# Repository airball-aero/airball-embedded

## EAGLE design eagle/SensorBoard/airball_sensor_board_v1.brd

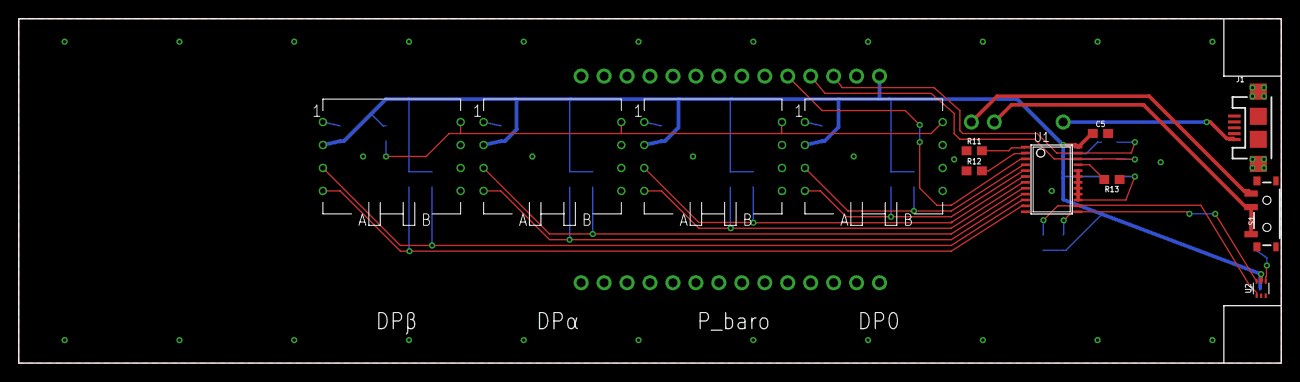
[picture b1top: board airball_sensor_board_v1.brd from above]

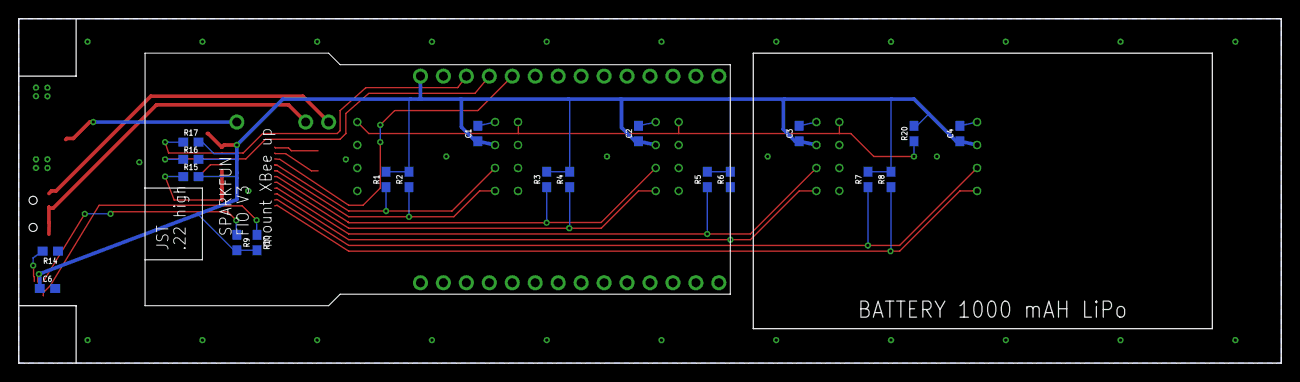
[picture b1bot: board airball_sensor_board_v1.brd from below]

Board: 2 copper layers, 139.7 x 38.1 mm, 33 parts (21 on the bottom side), 24 nets.

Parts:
C1, C2, C3, C4, C5, C6: 4.7uF; 0603
J1: USB-MICROB
R1, R2, R3, R4, R5, R6, R7, R8, R9, R10, R11, R12, R13, R14, R15, R16, R17, R20: 4.7k; 0603
S1: SWITCH_SPST_SMD_A
U1: TSSOP24
U2: TMP102; SOT563
U$2: SPARKFUN_FIO_V3
UP1, UP2, UP3, UP4: ALL_SENSORS_E1BD_8PIN_THRU

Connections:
#I2C_RST: U1.3, U$2.P$5
GND: C1.2, C2.2, C3.2, C4.2, C5.2, C6.2, J1.GND, R11.1, R12.1, R13.1, R14.1, U1.12, U2.2, U$2.P$2, U$2.P$28, UP1.P$1, UP2.P$1, UP3.P$1, UP4.P$1
unnamed: R1.1, U1.4, UP1.P$3
unnamed: R2.1, U1.5, UP1.P$4
unnamed: R3.1, U1.6, UP2.P$3
unnamed: R4.1, U1.7, UP2.P$4
unnamed: R5.1, U1.8, UP3.P$3
unnamed: R6.1, U1.9, UP3.P$4
unnamed: R7.1, U1.10, UP4.P$3
unnamed: R8.1, U1.11, UP4.P$4
unnamed: S1.1, U$2.P$29
unnamed: J1.VBUS, U$2.P$31
unnamed: R13.2, U1.21
unnamed: R12.2, U1.2
unnamed: R11.2, U1.1
unnamed: R20.1, UP1.P$8, UP2.P$8, UP3.P$8, UP4.P$8
unnamed: R9.1, U1.13, U2.6
unnamed: R10.1, U1.14, U2.1
unnamed: S1.2, S1.3, U$2.P$30
unnamed: R14.2, U2.4
unnamed: R15.1, U1.15, U1.16, U1.17, U1.18, U1.19, U1.20
SCL_IN: R16.1, U1.22, U$2.P$4
SDA_IN: R17.1, U1.23, U$2.P$3
VCC: C1.1, C2.1, C3.1, C4.1, C5.1, C6.1, R1.2, R2.2, R3.2, R4.2, R5.2, R6.2, R7.2, R8.2, R9.2, R10.2, R15.2, R16.2, R17.2, R20.2, U1.24, U2.5, U$2.P$1, U$2.P$26, UP1.P$2, UP2.P$2, UP3.P$2, UP4.P$2

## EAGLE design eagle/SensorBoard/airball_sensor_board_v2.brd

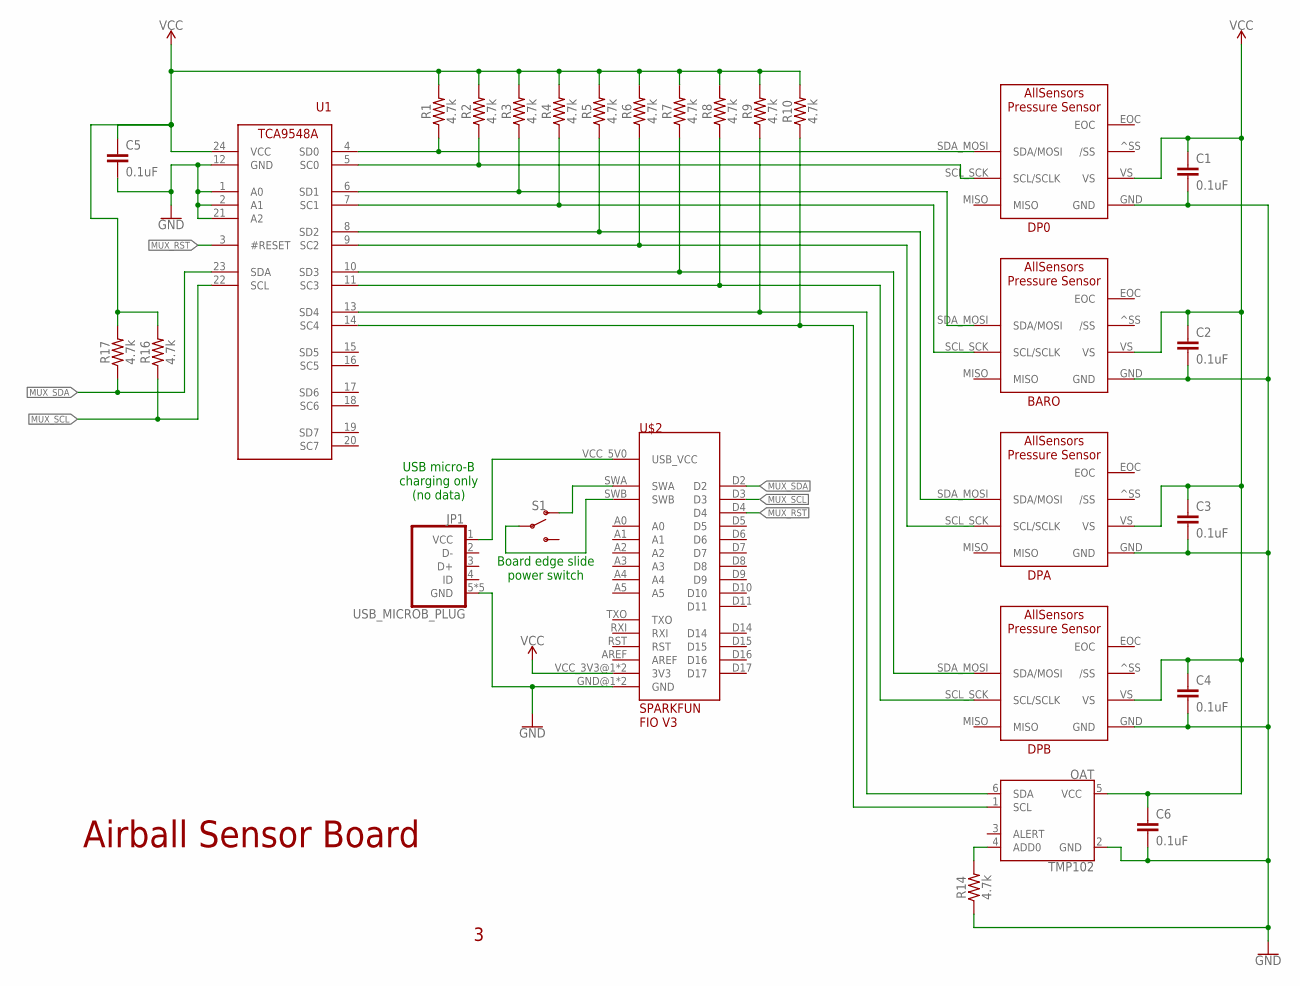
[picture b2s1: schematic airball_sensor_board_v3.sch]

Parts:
BARO: ALL_SENSORS_DLHR_E1ND; ALL_SENSORS_E1BD_8PIN_THRU
C1, C2, C3, C4, C5, C6: 0.1uF; 0603
DP0: ALL_SENSORS_DLHR_E1ND; ALL_SENSORS_E1BD_8PIN_THRU
DPA: ALL_SENSORS_DLHR_E1ND; ALL_SENSORS_E1BD_8PIN_THRU
DPB: ALL_SENSORS_DLHR_E1ND; ALL_SENSORS_E1BD_8PIN_THRU
JP1: USB_MICROB_PLUG; USB_MICRO_B_TYCO
OAT: TMP102; SOT563
R1, R2, R3, R4, R5, R6, R7, R8, R9, R10, R14, R16, R17: 4.7k; 0603
S1: SWITCH-SPDT-SMD-RIGHT-ANGLE; SWITCH_SPST_SMD_A
U1: TCA9548ATSSOP24; TSSOP24
U$2: SPARKFUN_FIO_V3

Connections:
GND: BARO.GND, C1.2, C2.2, C3.2, C4.2, C5.2, C6.2, DP0.GND, DPA.GND, DPB.GND, JP1.5 (GND), JP1.SH@1 (GND), JP1.SH@2 (GND), JP1.SH@3 (GND), JP1.SH@4 (GND), OAT.2 (GND), R14.1, U1.1 (A0), U1.2 (A1), U1.12 (GND), U1.21 (A2), U$2.GND@1 (GND), U$2.GND@2 (GND)
MUX_RST: U1.3 (#RESET), U$2.D4
MUX_SCL: R16.1, U1.22 (SCL), U$2.D3
MUX_SDA: R17.1, U1.23 (SDA), U$2.D2
OAT_ADD0: OAT.4 (ADD0), R14.2
SCL_BARO: BARO.SCL_SCK (SCL/SCLK), R4.1, U1.7 (SC1)
SCL_DP0: DP0.SCL_SCK (SCL/SCLK), R2.1, U1.5 (SC0)
SCL_DPA: DPA.SCL_SCK (SCL/SCLK), R6.1, U1.9 (SC2)
SCL_DPB: DPB.SCL_SCK (SCL/SCLK), R8.1, U1.11 (SC3)
SCL_OAT: OAT.1 (SCL), R10.1, U1.14 (SC4)
SDA_BARO: BARO.SDA_MOSI (SDA/MOSI), R3.1, U1.6 (SD1)
SDA_DP0: DP0.SDA_MOSI (SDA/MOSI), R1.1, U1.4 (SD0)
SDA_DPA: DPA.SDA_MOSI (SDA/MOSI), R5.1, U1.8 (SD2)
SDA_DPB: DPB.SDA_MOSI (SDA/MOSI), R7.1, U1.10 (SD3)
SDA_OAT: OAT.6 (SDA), R9.1, U1.13 (SD4)
SWA: S1.1 (O), U$2.SWA
SWB: S1.2, U$2.SWB
VCC_3V3: BARO.VS, C1.1, C2.1, C3.1, C4.1, C5.1, C6.1, DP0.VS, DPA.VS, DPB.VS, OAT.5 (VCC), R1.2, R2.2, R3.2, R4.2, R5.2, R6.2, R7.2, R8.2, R9.2, R10.2, R16.2, R17.2, U1.24 (VCC), U$2.VCC_3V3@1 (3V3), U$2.VCC_3V3@2 (3V3)
VCC_USB: JP1.1 (VCC), U$2.VCC_5V0 (USB_VCC)

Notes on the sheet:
USB micro-B charging only (no data)
Board edge slide power switch
Airball Sensor Board

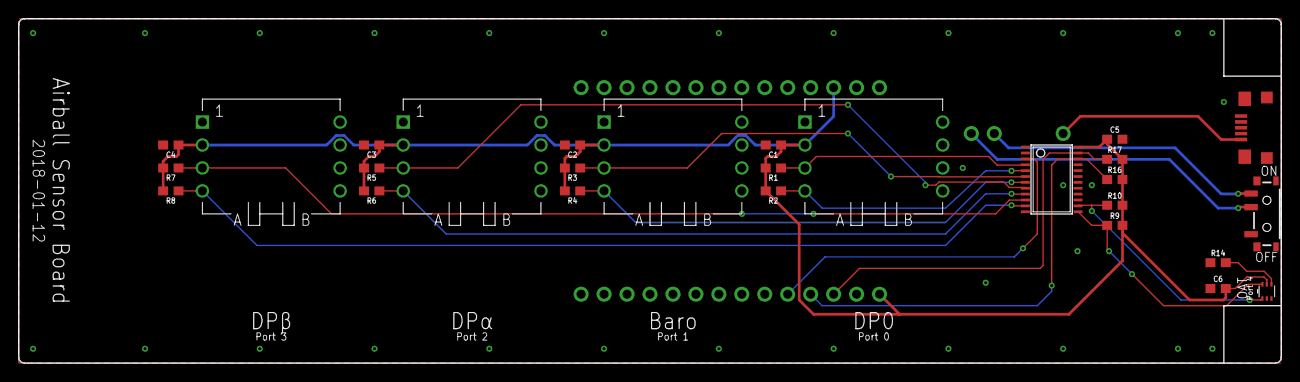
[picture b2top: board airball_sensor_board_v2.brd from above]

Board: 2 copper layers, 139.7 x 38.1 mm, 28 parts (1 on the bottom side), 19 nets.

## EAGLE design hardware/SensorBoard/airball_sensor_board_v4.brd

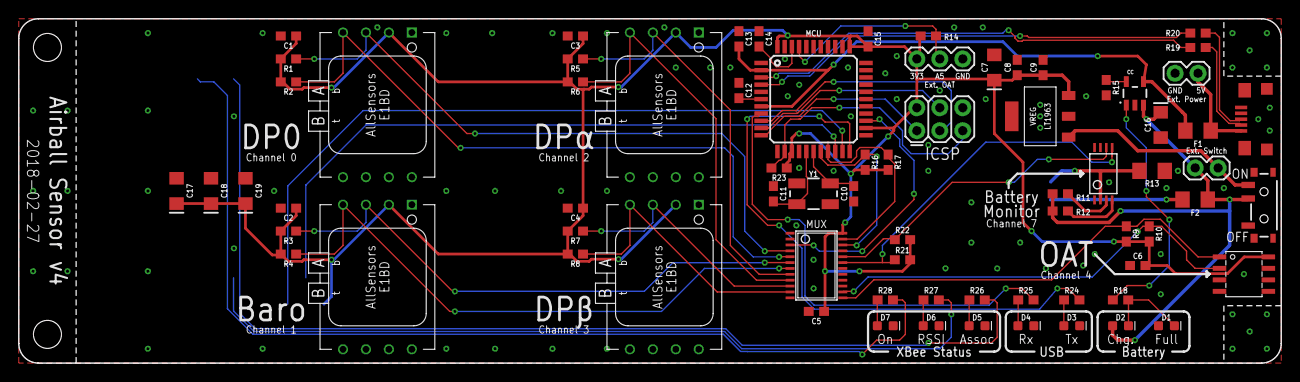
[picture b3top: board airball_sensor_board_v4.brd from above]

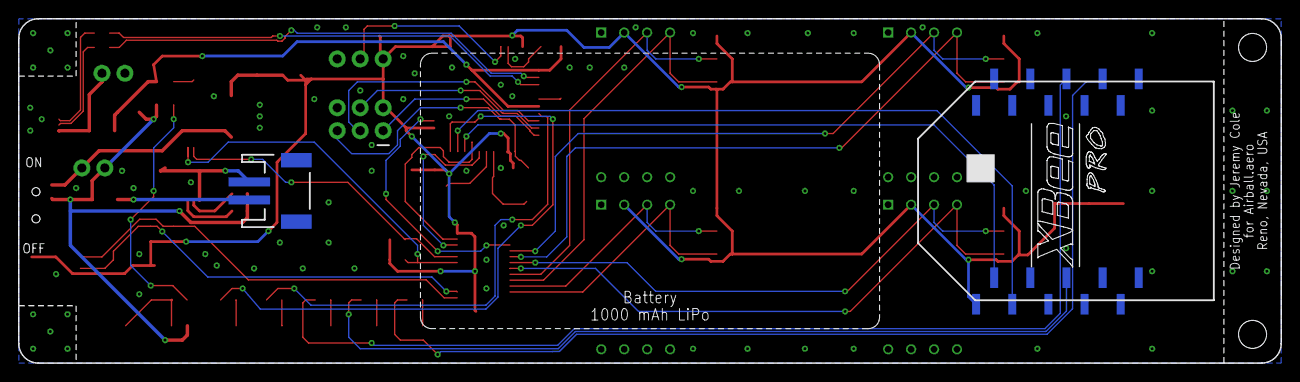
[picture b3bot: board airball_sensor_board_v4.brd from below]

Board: 2 copper layers, 139.7 x 38.1 mm, 76 parts (3 on the bottom side), 53 nets.

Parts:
BARO: ALLSENSORS_E1BD
BM: DS2782; TSSOP8
C1, C2, C3, C4, C5, C6, C9, C14, C15: 0.1uF; 0603
C7, C16, C17, C18, C19: 10uF; EIA3216
C8, C12, C13: 1.0uF; 0603
C10, C11: 22pF; 0603
CC: MCP73831; SOT23-5
D1, D2, D3, D4, D5, D6, D7: LED-0603
DP0: ALLSENSORS_E1BD
DPA: ALLSENSORS_E1BD
DPB: ALLSENSORS_E1BD
EXT_OAT: 1X03
EXT_POWER: 1X02
EXT_SW: 1X02
F1, F2: 6V/0.5A; 1206
ICSP: AVR_SPI_PROG_3X2PTH; 2X3
J1: JST-2-SMD
JP1: USB_MICROB_PLUG; USB_MICRO_B_TYCO
MCU: 32U4; TQFP44
MUX: TSSOP24
OAT: TMP275; SOIC8
R1, R2, R3, R4, R5, R6, R7, R8, R9, R10, R14, R16, R17, R21, R22: 4.7k; 0603
R11: 1k; 0603
R12: 470; 0603
R13: 15m; 1206
R15: 2.0k; 0603
R18, R24, R25, R26, R27, R28: 330; 0603
R19, R20: 22; 0603
R23: 10k; 0603
S1: SWITCH_SPST_SMD_A
U$3: LIPO_BATTERY_OUTLINE-1000MAH; SPARKFUN_LIPO_1000MAH
VREG: LT1963; SOT223-3
XBEE: XBEE-PRO-SMD
Y1: 8MHz; CRYSTAL-SMD-5X3.2-4PAD

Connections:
ASSOC_LED: R26.2, XBEE.15
BAT+: C16.+, CC.3, D2.A, EXT_SW.1, F2.2, R11.2, R12.2, S1.2
BAT+_UF: F2.1, J1.2
BAT-: BM.2, J1.1, R13.1
BAT_VRAW: EXT_SW.2, S1.1, VREG.1
BM_VDD: BM.4, R12.1
BM_VIN: BM.3, R11.1
CC_PROG: CC.5, R15.2
CHG_LED: CC.1, R18.1
EXT_OAT: EXT_OAT.2, MCU.41, R14.1
GND: BARO.1, BM.7, C1.2, C2.2, C3.2, C4.2, C5.2, C6.2, C7.-, C8.2, C9.2, C10.1, C11.1, C12.1, C13.1, C14.1, C15.1, C16.-, C17.-, C18.-, C19.-, CC.2, D1.A, D3.C, D4.C, D5.C, D6.C, D7.C, DP0.1, DPA.1, DPB.1, EXT_OAT.3, EXT_POWER.2, ICSP.6, JP1.5, JP1.SH@1, JP1.SH@2, JP1.SH@3, JP1.SH@4, MCU.5, MCU.15, MCU.23, MCU.33, MCU.35, MCU.43, MUX.1, MUX.2, MUX.12, MUX.21, OAT.4, OAT.5, OAT.6, OAT.7, R13.2, R15.1, VREG.2, VREG.TAB, XBEE.10
MISO: ICSP.1, MCU.11
MOSI: ICSP.4, MCU.10
MUX_RST: MCU.25, MUX.3
MUX_SCL: MCU.18, MUX.22, R16.1
MUX_SDA: MCU.19, MUX.23, R17.1
unnamed: D1.C, D2.C, R18.2
unnamed: C10.2, MCU.17, Y1.3
unnamed: C11.2, MCU.16, Y1.1
unnamed: D3.A, R24.1
unnamed: C14.2, MCU.42
unnamed: D4.A, R25.1
unnamed: C12.2, MCU.6
unnamed: D5.A, R26.1
unnamed: D6.A, R27.1
unnamed: D7.A, R28.1
ON_LED: R28.2, XBEE.13
RSSI_LED: R27.2, XBEE.6
RST: ICSP.5, MCU.13, R23.2
RXD: MCU.20, XBEE.2
RX_LED: MCU.8, R25.2
SCK: ICSP.3, MCU.9
SCL_BARO: BARO.4, MUX.7, R4.1
SCL_BM: BM.6, MUX.20, R22.1
SCL_DP0: DP0.4, MUX.5, R2.1
SCL_DPA: DPA.4, MUX.9, R6.1
SCL_DPB: DPB.4, MUX.11, R8.1
SCL_OAT: MUX.14, OAT.2, R10.1
SDA_BARO: BARO.3, MUX.6, R3.1
SDA_BM: BM.5, MUX.19, R21.1
SDA_DP0: DP0.3, MUX.4, R1.1
SDA_DPA: DPA.3, MUX.8, R5.1
SDA_DPB: DPB.3, MUX.10, R7.1
SDA_OAT: MUX.13, OAT.1, R9.1
TXD: MCU.21, XBEE.3
TX_LED: MCU.22, R24.2
USB_5V0_UF: EXT_POWER.1, F1.1, JP1.1
USB_N: MCU.3, R19.2
USB_P: MCU.4, R20.2
USB_X_N: JP1.2, R19.1
USB_X_P: JP1.3, R20.1
VCC_3V3: BARO.2, C1.1, C2.1, C3.1, C4.1, C5.1, C6.1, C7.+, C8.1, C9.1, C15.2, C17.+, C18.+, C19.+, DP0.2, DPA.2, DPB.2, EXT_OAT.1, ICSP.2, MCU.14, MCU.24, MCU.34, MCU.44, MUX.24, OAT.8, R1.2, R2.2, R3.2, R4.2, R5.2, R6.2, R7.2, R8.2, R9.2, R10.2, R14.2, R16.2, R17.2, R21.2, R22.2, R23.1, VREG.3, XBEE.1
VCC_5V0: C13.2, CC.4, F1.2, MCU.2, MCU.7

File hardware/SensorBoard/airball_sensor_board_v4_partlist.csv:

Partlist

Exported from airball_sensor_board_v4.brd at 2/25/20 10:12 PM

EAGLE Version 9.5.2 Copyright (c) 1988-2019 Autodesk, Inc.

Assembly variant: 

Part      Value               Package                Library             Position (mil)        Orientation

BARO                          ALLSENSORS_E1BD        airball             (1562.5 375)          R270
BM        DS2782              TSSOP8                 airball             (4725 825)            R0
C1        0.1uF               0603                   SparkFun-Capacitors (1175 1425)           R180
C2        0.1uF               0603                   SparkFun-Capacitors (1175 675)            R180
C3        0.1uF               0603                   SparkFun-Capacitors (2425 1425)           R180
C4        0.1uF               0603                   SparkFun-Capacitors (2425 675)            R180
C5        0.1uF               0603                   SparkFun-Capacitors (3475 225)            R180
C6        0.1uF               0603                   SparkFun-Capacitors (4875 425)            R180
C7        10uF                EIA3216                SparkFun-Capacitors (4250 1287.5)         R270
C8        1.0uF               0603                   SparkFun-Capacitors (4350 1287.5)         R90
C9        0.1uF               0603                   SparkFun-Capacitors (4462.5 1287.5)       R90
C10       22pF                0603                   SparkFun-Capacitors (3637.5 737.5)        R90
C11       22pF                0603                   SparkFun-Capacitors (3287.5 737.5)        R270
C12       1.0uF               0603                   SparkFun-Capacitors (3137.5 1187.5)       R270
C13       1.0uF               0603                   SparkFun-Capacitors (3137.5 1412.5)       R270
C14       0.1uF               0603                   SparkFun-Capacitors (3225 1412.5)         R270
C15       0.1uF               0603                   SparkFun-Capacitors (3700 1412.5)         R270
C16       10uF                EIA3216                SparkFun-Capacitors (4975 1037.5)         R90
C17       10uF                EIA3216                SparkFun-Capacitors (687.5 750)           R270
C18       10uF                EIA3216                SparkFun-Capacitors (837.5 750)           R270
C19       10uF                EIA3216                SparkFun-Capacitors (987.5 750)           R270
CC        MCP73831            SOT23-5                SparkFun-IC-Power   (4862.5 1175)         R0
D1                            LED-0603               SparkFun-LED        (5000 162.5)          R0
D2                            LED-0603               SparkFun-LED        (4800 162.5)          R0
D3                            LED-0603               SparkFun-LED        (4587.5 162.5)        R0
D4                            LED-0603               SparkFun-LED        (4387.5 162.5)        R0
D5                            LED-0603               SparkFun-LED        (4175 162.5)          R0
D6                            LED-0603               SparkFun-LED        (3975 162.5)          R0
D7                            LED-0603               SparkFun-LED        (3775 162.5)          R0
DP0                           ALLSENSORS_E1BD        airball             (1562.5 1125)         R270
DPA                           ALLSENSORS_E1BD        airball             (2812.5 1125)         R270
DPB                           ALLSENSORS_E1BD        airball             (2812.5 375)          R270
EXT_OAT                       1X03                   SparkFun-Connectors (3912.5 1325)         R0
EXT_POWER                     1X02                   SparkFun-Connectors (5137.5 1262.5)       R180
EXT_SW                        1X02                   SparkFun-Connectors (5125 850)            R0
F1        6V/0.5A             1206                   SparkFun-Fuses      (5137.5 1012.5)       R180
F2        6V/0.5A             1206                   SparkFun-Fuses      (5125 712.5)          R0
ICSP      AVR_SPI_PROG_3X2PTH 2X3                    SparkFun-Connectors (3912.5 1012.5)       R0
J1                            JST-2-SMD              SparkFun-Connectors (4350 750)            MR270
JP1       USB_MICROB_PLUG     USB_MICRO_B_TYCO       airball             (5437.5 1062.5)       R90
MCU       32U4                TQFP44                 jcole               (3462.5 1150)         R0
MUX                           TSSOP24                airball             (3475 425)            R270
OAT       TMP275              SOIC8                  airball             (5337.5 387.5)        R270
R1        4.7k                0603                   SparkFun-Resistors  (1175 1325)           R180
R2        4.7k                0603                   SparkFun-Resistors  (1175 1225)           R180
R3        4.7k                0603                   SparkFun-Resistors  (1175 575)            R180
R4        4.7k                0603                   SparkFun-Resistors  (1175 475)            R180
R5        4.7k                0603                   SparkFun-Resistors  (2425 1325)           R180
R6        4.7k                0603                   SparkFun-Resistors  (2425 1225)           R180
R7        4.7k                0603                   SparkFun-Resistors  (2425 575)            R180
R8        4.7k                0603                   SparkFun-Resistors  (2425 475)            R180
R9        4.7k                0603                   SparkFun-Resistors  (4825 562.5)          R270
R10       4.7k                0603                   SparkFun-Resistors  (4925 562.5)          R270
R11       1k                  0603                   SparkFun-Resistors  (4537.5 737.5)        R180
R12       470                 0603                   SparkFun-Resistors  (4537.5 662.5)        R180
R13       15m                 1206                   SparkFun-Resistors  (4937.5 837.5)        R0
R14       4.7k                0603                   SparkFun-Resistors  (3962.5 1425)         R180
R15       2.0k                0603                   SparkFun-Resistors  (4737.5 1200)         R90
R16       4.7k                0603                   SparkFun-Resistors  (3687.5 875)          R270
R17       4.7k                0603                   SparkFun-Resistors  (3787.5 875)          R270
R18       330                 0603                   SparkFun-Resistors  (4800 275)            R0
R19       22                  0603                   SparkFun-Resistors  (5137.5 1375)         R180
R20       22                  0603                   SparkFun-Resistors  (5137.5 1437.5)       R180
R21       4.7k                0603                   SparkFun-Resistors  (3850 450)            R0
R22       4.7k                0603                   SparkFun-Resistors  (3850 537.5)          R0
R23       10k                 0603                   SparkFun-Resistors  (3312.5 850)          R180
R24       330                 0603                   SparkFun-Resistors  (4587.5 275)          R0
R25       330                 0603                   SparkFun-Resistors  (4387.5 275)          R0
R26       330                 0603                   SparkFun-Resistors  (4175 275)            R0
R27       330                 0603                   SparkFun-Resistors  (3975 275)            R0
R28       330                 0603                   SparkFun-Resistors  (3775 275)            R0
S1                            SWITCH_SPST_SMD_A      SparkFun-Switches   (5425 687.5)          R270
VREG      LT1963              SOT223-3               airball             (4450 1075)           R90
XBEE      XBEE-PRO-SMD        XBEE-PRO-SMD           airball             (975 750)             MR90
Y1        8MHz                CRYSTAL-SMD-5X3.2-4PAD SparkFun-Clocks     (3462.5 737.5)        R0

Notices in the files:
parts and their libraries:
SparkFun-Capacitors: Licensing: Creative Commons ShareAlike 4.0 International - https://creativecommons.org/licenses/by-sa/4.0
